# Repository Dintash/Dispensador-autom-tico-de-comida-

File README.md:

## INTEGRANTES:
Andrés David Giraldo Gutiérrez

Samuel Felipe Correales Díaz

Breiner Villota

# Resumen:
Este proyecto fue concebido con el propósito de hacer una contribución significativa a la sociedad. Además de su impacto social, también ha representado una fuente invaluable de desarrollo de habilidades en diversos campos. En particular, hemos experimentado un crecimiento exponencial en el ámbito de la electrónica, consolidando nuestro conocimiento y competencia en esta área.

El papel del profesor ha sido crucial al impulsarnos hacia la autonomía individual, fomentando la capacidad de abordar desafíos de manera independiente. Este enfoque no solo fortalece nuestras habilidades técnicas, sino que también cultiva la confianza en nuestras capacidades individuales.

Asimismo, este proyecto ha sido una plataforma para el desarrollo de habilidades blandas esenciales, como la responsabilidad, compañerismo y cooperación. Estos aspectos son fundamentales tanto en el ámbito profesional como en el personal, y su mejora demuestra un compromiso integral con nuestro crecimiento como individuos y como equipo.

En el próximo periodo, podríamos considerar la posibilidad de compartir nuestra experiencia y conocimientos con otros, ya que esto no solo fortalecerá nuestra conexión con la comunidad, sino que también puede servir como inspiración para aquellos que buscan emprender proyectos similares.
Cabe recalcar que este proyecto no tiene aguna complejidad a la hora de su funcionalidad por tanto se apto para todo tipo de cliente 

# PROCESO
Primero se genero conocimiento sobre que eran los micro-controladres y como usarlo, también realizamos pruebas con diferentes componente electrónicos, tales como, led, motores, foto resistencias, entre otros, de segundo lugar, empezamos a pensar algún proyecto que lograramos hacer durante el periodo académico, decidio el proyecto realizamos algunas herramientas con el fin de saber como funciona y con que funciona, ya con esto definido, nos enfocabamos en probar los componentes electrónicos que debía tener el proyecto,ya que, para un buen desarrollo debiamos saber como funcionaban, en tercer lugar, nos dieron una introducción en lo más importante de el proyecto la PCB y la programación que fue por medio de MYCROPYTHON, la PCB es la que permite que los compoenentes estén conectados sin necesidad de un protoboard la cual necesitaría muchos jumpers para que todo esté conectado correctamente, cabe recalcar que se tuvo algunas complicaciones a la hora de la programación de algunos componenetes, pero gracias a una buena toma de decisionse entre los integrantes del equipo se logro superar aquella complicación, para la última parte del proceso se genero la PCB por KICAT gracias a el conocimiento adquerido, con la PCB hecha se realizo la creación de las piezas del proyecto para emsamblarlas y darlo por terminado.

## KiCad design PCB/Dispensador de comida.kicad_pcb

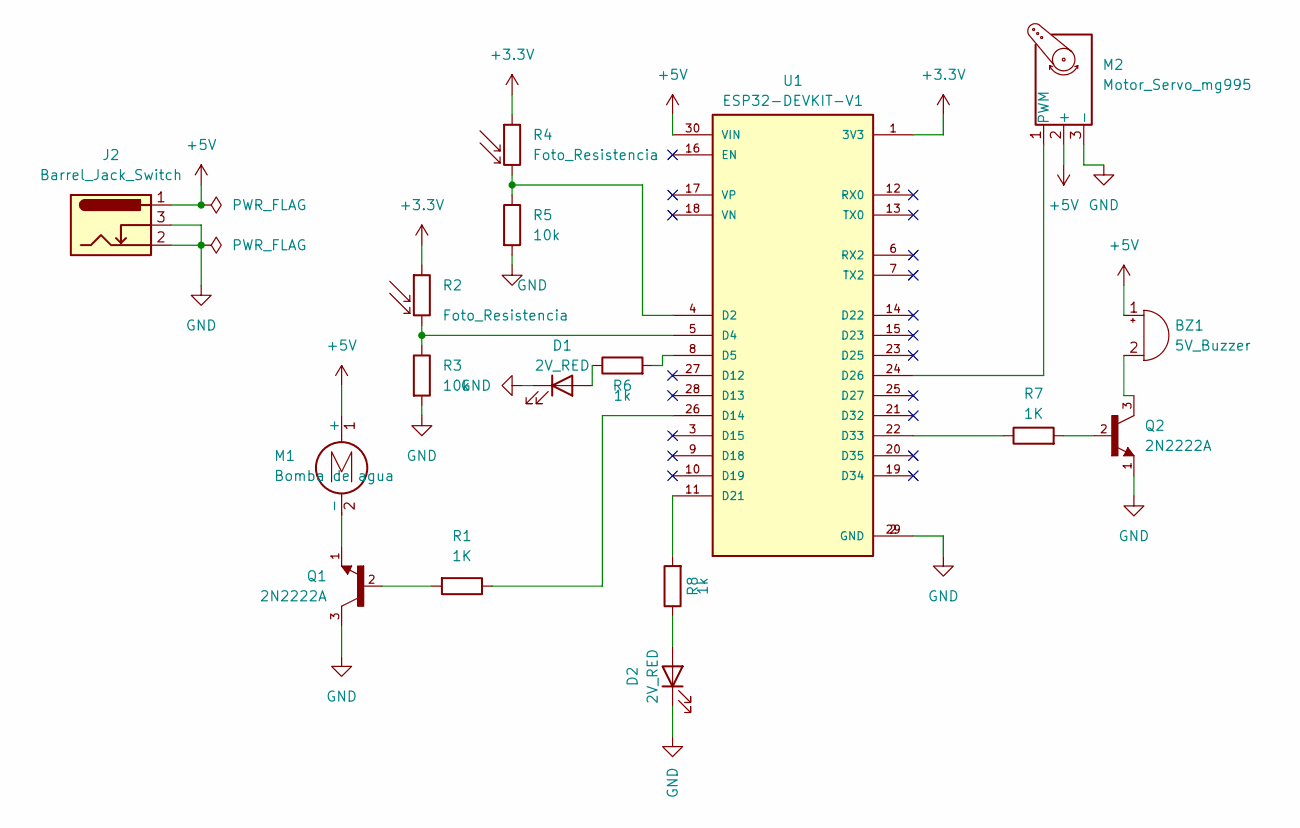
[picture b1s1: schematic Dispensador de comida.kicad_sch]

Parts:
BZ1: 5V_Buzzer; Buzzer_15x7.5RM7.6
D1, D2: 2V_RED; LED_D5.0mm
J2: Barrel_Jack_Switch; BarrelJack_Horizontal
M1: Bomba de agua; PinSocket_1x02_P2.54mm_Vertical
M2: Motor_Servo_mg995; PinHeader_1x03_P2.54mm_Vertical
Q1, Q2: 2N2222A; TO-92; PARTREV 2
R1, R7: 1K; R_Axial_DIN0207_L6.3mm_D2.5mm_P7.62mm_Horizontal
R2, R4: Foto_Resistencia; R_LDR_5.0x4.1mm_P3mm_Vertical
R3, R5: 10k; R_Axial_DIN0207_L6.3mm_D2.5mm_P7.62mm_Horizontal
R6, R8: 1k; R_Axial_DIN0207_L6.3mm_D2.5mm_P7.62mm_Horizontal
U1: ESP32-DEVKIT-V1; MODULE_ESP32_DEVKIT_V1; PARTREV N/A

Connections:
+3.3V: R2.1, R4.1, U1.1 (3V3)
+5V: BZ1.1 (-), J2.1, M1.1 (+), M2.2 (+), U1.30 (VIN)
GND: D1.1 (K), D2.1 (K), J2.2, J2.3, M2.3 (-), Q1.3, Q2.1, R3.2, R5.2, U1.2 (GND), U1.29 (GND)
unnamed: BZ1.2 (+), Q2.3
unnamed: D1.2 (A), R6.1
unnamed: D2.2 (A), R8.1
unnamed: M1.2 (-), Q1.1
unnamed: M2.1 (PWM), U1.24 (D26)
unnamed: Q1.2, R1.2
unnamed: Q2.2, R7.2
unnamed: R4.2, R5.1, U1.4 (D2)
unnamed: R2.2, R3.1, U1.5 (D4)
unnamed: R6.2, U1.8 (D5)
unnamed: R1.1, U1.26 (D14)
unnamed: R8.2, U1.11 (D21)
unnamed: R7.1, U1.22 (D33)

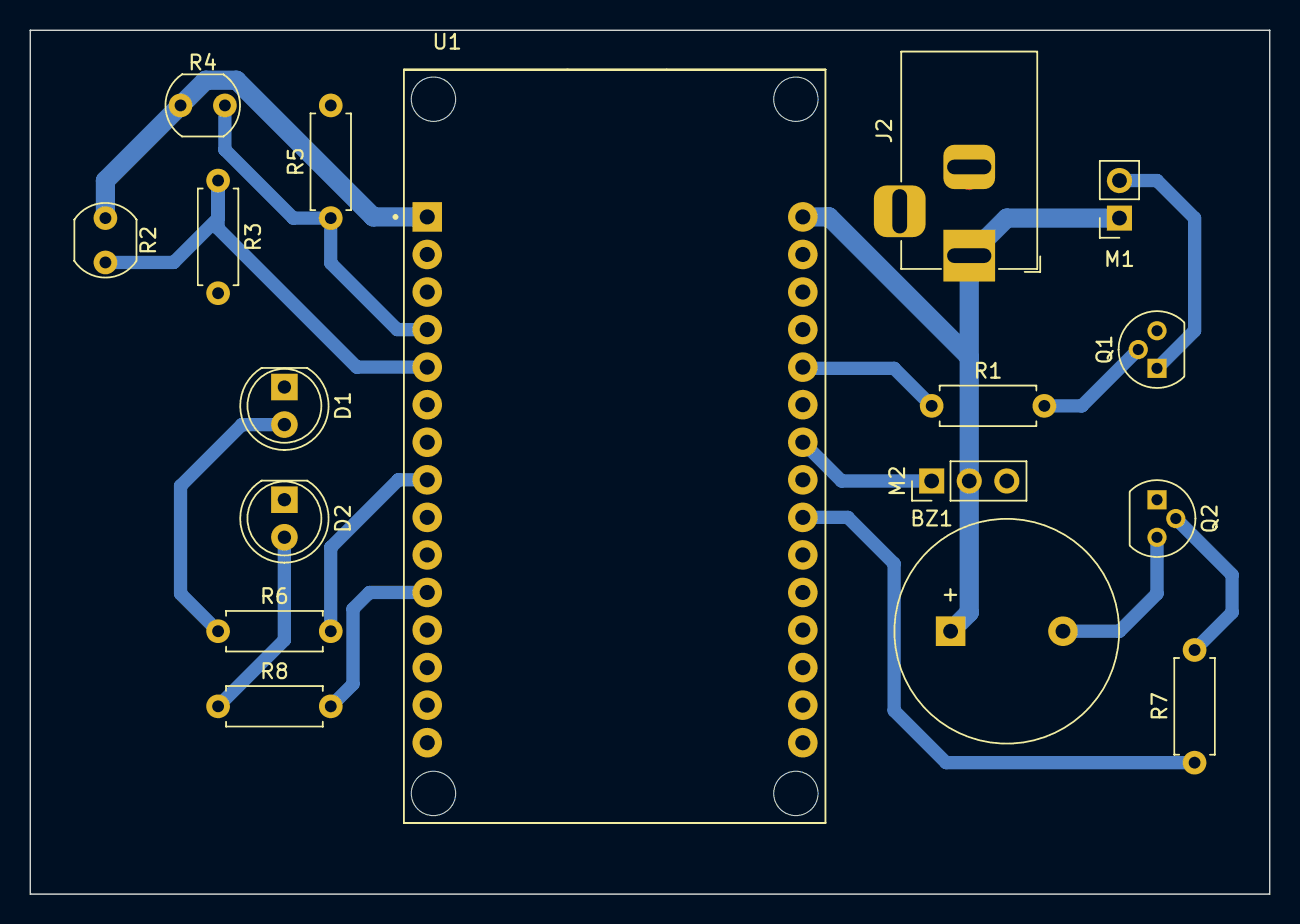
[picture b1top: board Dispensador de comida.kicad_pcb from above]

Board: 2 copper layers, 83.8 x 58.4 mm, 17 parts (0 on the bottom side), 16 nets.

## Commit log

2023-12-01 DIAGRAMAS
2023-12-01 EVIDENCIAS
2023-12-01 BOCETOS
2023-12-01 VIDEO FINAL
2023-12-01 CÓDIGO.PY
